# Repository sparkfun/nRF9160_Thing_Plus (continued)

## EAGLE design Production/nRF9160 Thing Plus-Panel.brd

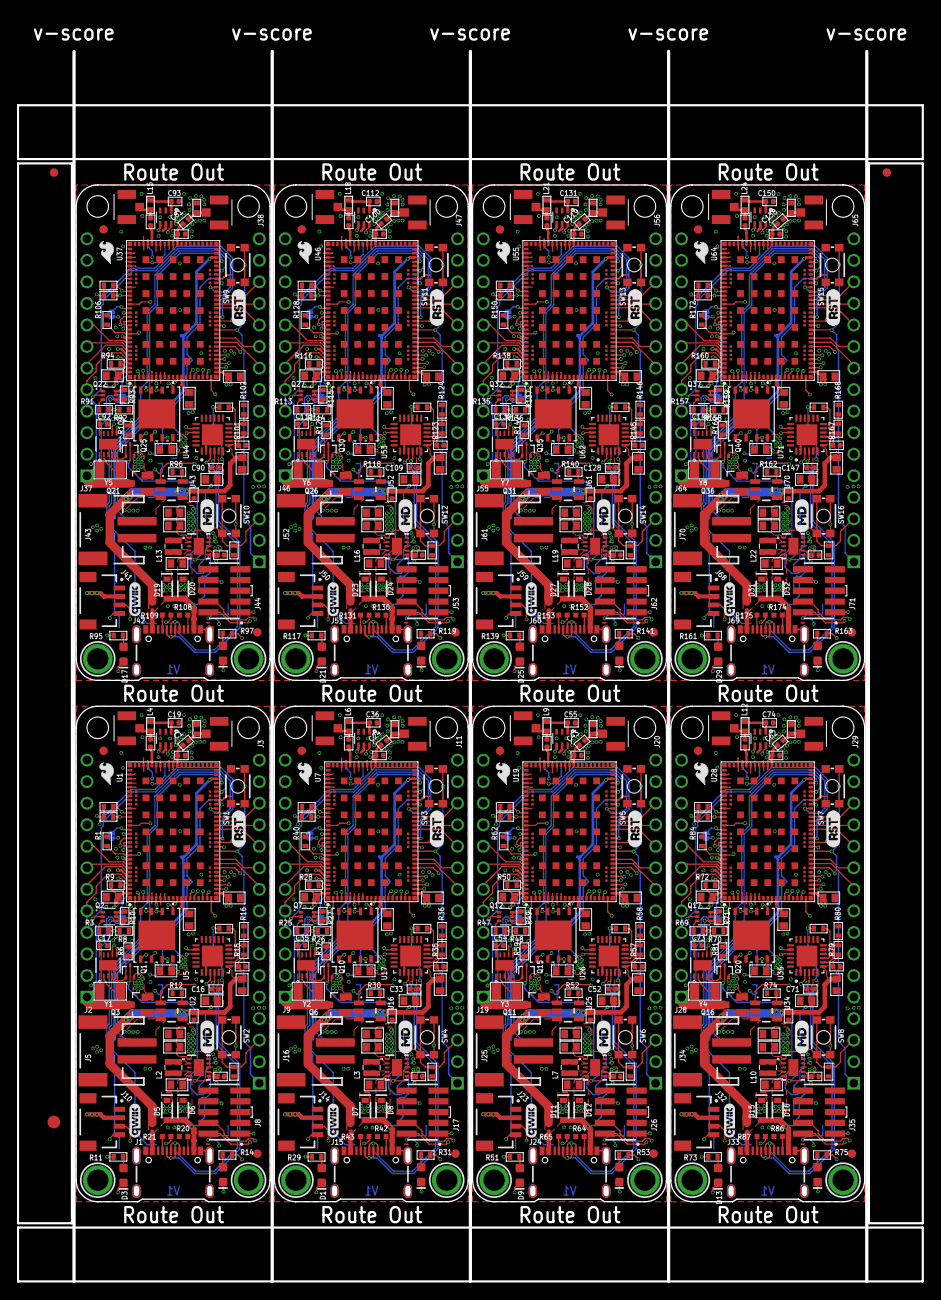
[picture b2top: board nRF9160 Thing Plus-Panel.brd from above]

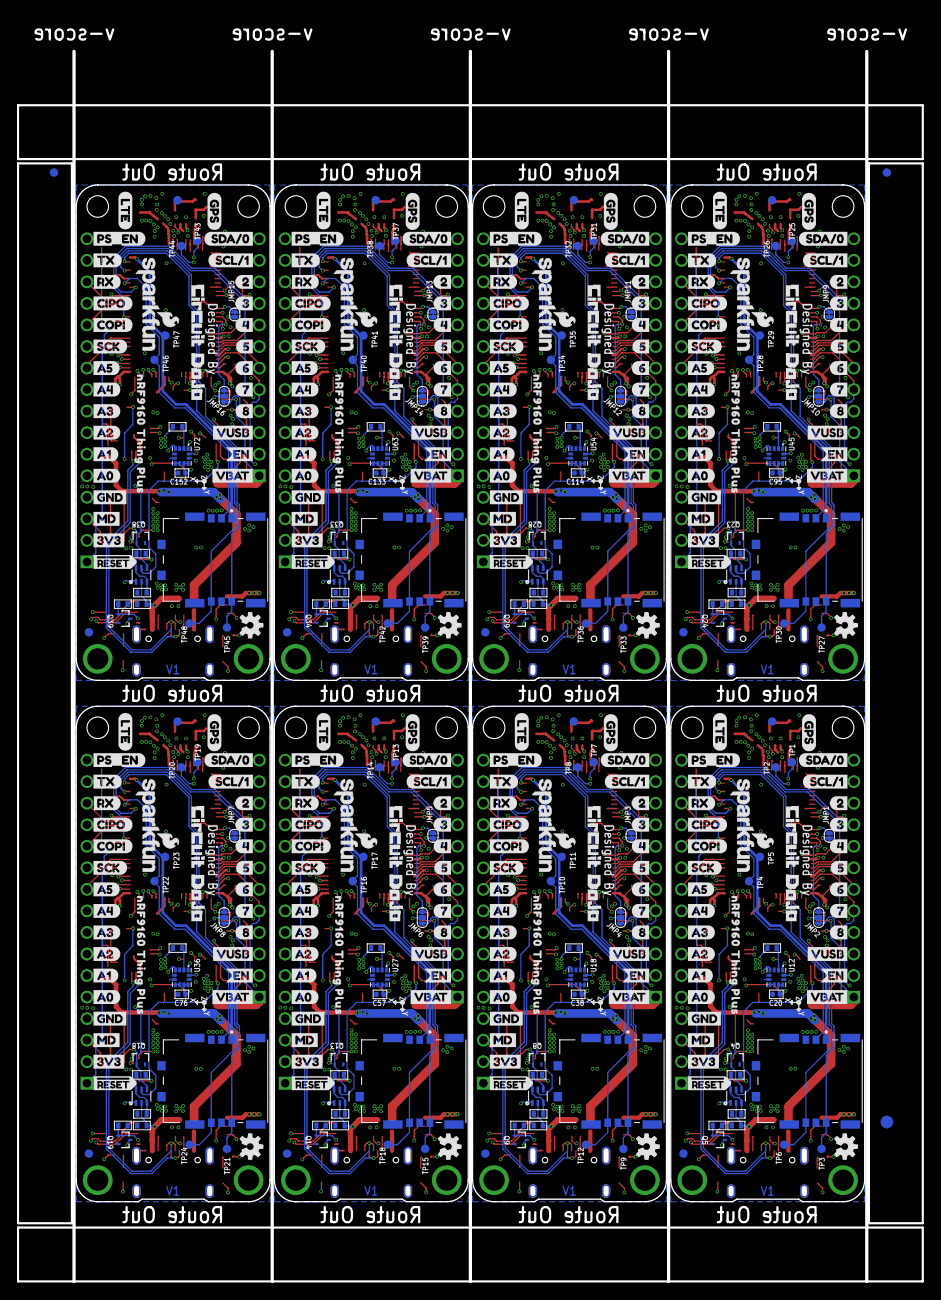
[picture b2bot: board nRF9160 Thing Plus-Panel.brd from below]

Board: 4 copper layers, 106.7 x 145.0 mm, 1030 parts (443 on the bottom side), 632 nets.

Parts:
C1, C2, C24, C37, C43, C56, C62, C75, C81, C94, C100, C113, C119, C132, C138, C151: 15p; CAPC1005X55N
C3, C8, C9, C10, C13, C15, C25, C26, C27, C28, C30, C32, C44, C45, C46, C47, C49, C51, C63, C64, C65, C66, C68, C70, C82, C83, C84, C85, C87, C89, C101, C102, C103, C104, C106, C108, C120, C121, C122, C123, C125, C127, C139, C140, C141, C142, C144, C146: 4.7u; C0603
C4, C5, C7, C18, C21, C22, C39, C40, C41, C58, C59, C60, C77, C78, C79, C96, C97, C98, C115, C116, C117, C134, C135, C136: 10u; C0603
C6, C14, C16, C17, C20, C23, C31, C33, C35, C38, C42, C50, C52, C54, C57, C61, C69, C71, C73, C76, C80, C88, C90, C92, C95, C99, C107, C109, C111, C114, C118, C126, C128, C130, C133, C137, C145, C147, C149, C152: 0.1u; CAPC1005X55N
C11, C29, C48, C67, C86, C105, C124, C143: 1u; CAPC1005X55N
C12, C19, C34, C36, C53, C55, C72, C74, C91, C93, C110, C112, C129, C131, C148, C150: 56p; CAPC1005X55N
D1, D3, D9, D13, D17, D21, D25, D29: BLUE; LED-0603
D2, D4, D10, D14, D18, D22, D26, D30: Yellow; LED-0603
D5, D6, D7, D8, D11, D12, D15, D16, D19, D20, D23, D24, D27, D28, D31, D32: 1A/23V/620mV; SOD-323
E$1, E$2, E$3, E$4: FIDUCIAL-1X2
E$5, E$6: FIDUCIAL-1.5X3
J1, J15, J24, J33, J42, J51, J60, J69: USB Female C; USB-C-16P_4LAYER-PADS
J2, J9, J19, J28, J37, J46, J55, J64: CON-HEADER-1X12-MALE-PIN
J3, J11, J20, J29, J38, J47, J56, J65: CON-HEADER-1X16-MALE-PIN
J4, J7, J12, J13, J21, J22, J30, J31, J39, J40, J48, J49, J57, J58, J66, J67: CON-1909763-1; TE_1909763-1
J5, J16, J25, J34, J43, J52, J61, J70: JST-2-SMD
J6, J18, J27, J36, J45, J54, J63, J72: CON-SIM-104224-0820; MOLEX_104224-0820
J8, J17, J26, J35, J44, J53, J62, J71: CON-FTSH-105-XX-X-DV; SAMTEC_FTSH-105-XX-X-DV
J10, J14, J23, J32, J41, J50, J59, J68: QWIIC_RIGHT_ANGLE; JST04_1MM_RA
JMP1, JMP3, JMP5, JMP7, JMP9, JMP11, JMP13, JMP15: JUMPER-NC; JUMPER-ROUND-NC
JMP2, JMP4, JMP6, JMP8, JMP10, JMP12, JMP14, JMP16: JUMPER-3/1; JUMPER-ROUND-3-NO-R
L1, L5, L8, L11, L14, L17, L20, L23: 39n; IND0402_22N_TAI
L2, L3, L7, L10, L13, L16, L19, L22: 1.5u; IND-2P0X2P0X1P2
L4, L6, L9, L12, L15, L18, L21, L24: 68n; IND0402_22N_TAI
LOGO1, LOGO2, LOGO3, LOGO4, LOGO5, LOGO6, LOGO7, LOGO8: OSHW-LOGOS; OSHW-LOGO-S
PCB1, PCB2, PCB3, PCB4, PCB5, PCB6, PCB7, PCB8: PCB-NRF91-FEATHER; PLACEHOLDER
Q1, Q10, Q15, Q20, Q25, Q30, Q35, Q40: MOSFET-P-SC89; DIO_RB558WMF-L
Q2, Q7, Q12, Q17, Q22, Q27, Q32, Q37: MOSFET-DUAL-COMP-SOT563; SOT50P160X60-6N
Q3, Q6, Q11, Q16, Q21, Q26, Q31, Q36: MOSFET-P-20V-4.7A-SOT23; SOT23
Q4, Q5, Q8, Q9, Q13, Q14, Q18, Q19, Q23, Q24, Q28, Q29, Q33, Q34, Q38, Q39: MOSFET-N-SC89; DIO_RB558WMF-L
R1, R3, R5, R6, R7, R8, R10, R13, R22, R23, R25, R26, R27, R32, R34, R37, R40, R44, R45, R47, R48, R49, R54, R56, R59, R62, R66, R67, R69, R70, R71, R76, R78, R81, R84, R88, R89, R91, R92, R93, R98, R100, R103, R106, R110, R111, R113, R114, R115, R120, R122, R125, R128, R132, R133, R135, R136, R137, R142, R144, R147, R150, R154, R155, R157, R158, R159, R164, R166, R169, R172, R176: 100k; R0402-M
R2, R9, R19, R24, R28, R41, R46, R50, R63, R68, R72, R85, R90, R94, R107, R112, R116, R129, R134, R138, R151, R156, R160, R173: 1M; R0402-M
R4, R33, R55, R77, R99, R121, R143, R165: 1k; R0402-M
R11, R14, R29, R31, R51, R53, R73, R75, R95, R97, R117, R119, R139, R141, R161, R163: 330; R0402-M
R12, R30, R52, R74, R96, R118, R140, R162: 2k; R0402-M
R15, R35, R57, R79, R101, R123, R145, R167: 22k; R0402-M
R16, R36, R58, R80, R102, R124, R146, R168: 33k; R0402-M
R17, R18, R38, R39, R60, R61, R82, R83, R104, R105, R126, R127, R148, R149, R170, R171: 10k; R0402-M
R20, R21, R42, R43, R64, R65, R86, R87, R108, R109, R130, R131, R152, R153, R174, R175: 5.1k; 0402-TIGHT
SW1, SW2, SW3, SW4, SW5, SW6, SW7, SW8, SW9, SW10, SW11, SW12, SW13, SW14, SW15, SW16: MOMENTARY-SWITCH-SPST-SMD-4.6X2.8MM; TACTILE_SWITCH_SMD_4.6X2.8MM
TP1, TP2, TP3, TP4, TP5, TP6, TP7, TP8, TP9, TP10, TP11, TP12, TP13, TP14, TP15, TP16, TP17, TP18, TP19, TP20, TP21, TP22, TP23, TP24, TP25, TP26, TP27, TP28, TP29, TP30, TP31, TP32, TP33, TP34, TP35, TP36, TP37, TP38, TP39, TP40, TP41, TP42, TP43, TP44, TP45, TP46, TP47, TP48: TP-1SIDE-1P0; TP-1P0
U1, U7, U19, U28, U37, U46, U55, U64: MOD-NRF9160-SICA-R; NORDIC_NRF9160-SICA-R
U2, U16, U25, U34, U43, U52, U61, U70: MCP73831; SOT23-5
U3, U11, U21, U30, U39, U48, U57, U66: IC-TPS63031DSKR; DSK0010A
U4, U15, U24, U33, U42, U51, U60, U69: POWER-SWITCH-MIC94092YC6; SOT363
U5, U17, U26, U35, U44, U53, U62, U71: IC-CP2102N-A02-GQFN24R; QFN50P400X400X80-25N
U6, U10, U20, U29, U38, U47, U56, U65: FLASH-WSON; WIN_ZP-8-L
U8, U13, U22, U31, U40, U49, U58, U67: IC-PCF85063ATL/1; DFN10_2P7X2P7-L
U9, U14, U23, U32, U41, U50, U59, U68: IC-BAV70S; SOT363
U12, U18, U27, U36, U45, U54, U63, U72: IC-LIS2DH12TR; PQFN50P200X200100-12N
U$1, U$66, U$127, U$171, U$215, U$259, U$303, U$347: SFE_LOGO_NAME_FLAME_.1
U$2, U$28, U$81, U$136, U$180, U$224, U$268, U$312: LOGO-CIRCUITDOJO
U$3, U$4, U$24, U$25, U$29, U$30, U$35, U$77, U$78, U$82, U$94, U$132, U$133, U$137, U$138, U$176, U$177, U$181, U$182, U$220, U$221, U$225, U$226, U$264, U$265, U$269, U$270, U$308, U$309, U$313, U$314, U$352: FIDUCIAL-1MM
U$5, U$33, U$95, U$139, U$183, U$227, U$271, U$315: A3L-LOC
U$6, U$34, U$96, U$140, U$184, U$228, U$272, U$316: QWIIC_4MM
U$7, U$61, U$122, U$166, U$210, U$254, U$298, U$342: RST0
U$8, U$67, U$128, U$172, U$216, U$260, U$304, U$348: PS_EN0
U$9, U$14, U$55, U$62, U$116, U$123, U$160, U$167, U$204, U$211, U$248, U$255, U$292, U$299, U$336, U$343: MD0
U$10, U$53, U$114, U$158, U$202, U$246, U$290, U$334: 20
U$11, U$54, U$115, U$159, U$203, U$247, U$291, U$335: 30
U$12, U$70, U$130, U$174, U$218, U$262, U$306, U$350: SCL#11
U$13, U$76, U$131, U$175, U$219, U$263, U$307, U$351: SDA#00
U$15, U$63, U$124, U$168, U$212, U$256, U$300, U$344: SFE_LOGO_FLAME_.1
U$16, U$56, U$117, U$161, U$205, U$249, U$293, U$337: TX0
U$17, U$57, U$118, U$162, U$206, U$250, U$294, U$338: RX0
U$18, U$58, U$119, U$163, U$207, U$251, U$295, U$339: SCK0
U$19, U$59, U$120, U$164, U$208, U$252, U$296, U$340: CIPO0
U$20, U$60, U$121, U$165, U$209, U$253, U$297, U$341: COPI0
U$21, U$64, U$125, U$169, U$213, U$257, U$301, U$345: GPS0
U$22, U$65, U$126, U$170, U$214, U$258, U$302, U$346: LTE0
U$23, U$68, U$129, U$173, U$217, U$261, U$305, U$349: NRF9160_THING_PLUS0
U$26, U$27, U$31, U$32, U$79, U$80, U$134, U$135, U$178, U$179, U$222, U$223, U$266, U$267, U$310, U$311: MOUNTING-HOLE-2.5MM-PLATED
U$36, U$69, U$97, U$141, U$185, U$229, U$273, U$317: GND12
U$37, U$71, U$98, U$142, U$186, U$230, U$274, U$318: 3V314
U$38, U$72, U$99, U$143, U$187, U$231, U$275, U$319: #RESET15
U$39, U$73, U$100, U$144, U$188, U$232, U$276, U$320: VUSB25
U$40, U$74, U$101, U$145, U$189, U$233, U$277, U$321: EN26
U$41, U$75, U$102, U$146, U$190, U$234, U$278, U$322: VBAT27
U$42, U$83, U$103, U$147, U$191, U$235, U$279, U$323: A56
U$43, U$84, U$104, U$148, U$192, U$236, U$280, U$324: A47
U$44, U$85, U$105, U$149, U$193, U$237, U$281, U$325: A38
U$45, U$86, U$106, U$150, U$194, U$238, U$282, U$326: A29
U$46, U$87, U$107, U$151, U$195, U$239, U$283, U$327: A110
U$47, U$88, U$108, U$152, U$196, U$240, U$284, U$328: A011
U$48, U$89, U$109, U$153, U$197, U$241, U$285, U$329: 412
U$49, U$90, U$110, U$154, U$198, U$242, U$286, U$330: 513
U$50, U$91, U$111, U$155, U$199, U$243, U$287, U$331: 614
U$51, U$92, U$112, U$156, U$200, U$244, U$288, U$332: 715
U$52, U$93, U$113, U$157, U$201, U$245, U$289, U$333: 816
Y1, Y2, Y3, Y4, Y5, Y6, Y7, Y8: XTAL-ABS07AIG-32.768KHZ-7-T; XTAL320X150X90

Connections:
!EN: J2.2, Q5.1, R19.2
!EN1: J9.2, Q9.1, R41.2
!EN2: J19.2, Q14.1, R63.2
!EN3: J28.2, Q19.1, R85.2
!EN4: J37.2, Q24.1, R107.2
!EN5: J46.2, Q29.1, R129.2
!EN6: J55.2, Q34.1, R151.2
!EN7: J64.2, Q39.1, R173.2
!RESET: J3.1, SW1.1, SW1.2, U1.32
!RESET1: J11.1, SW3.1, SW3.2, U7.32
!RESET2: J20.1, SW5.1, SW5.2, U19.32
!RESET3: J29.1, SW7.1, SW7.2, U28.32
!RESET4: J38.1, SW9.1, SW9.2, U37.32
!RESET5: J47.1, SW11.1, SW11.2, U46.32
!RESET6: J56.1, SW13.1, SW13.2, U55.32
!RESET7: J65.1, SW15.1, SW15.2, U64.32
+3V1: C18.1, C21.1, C25.1, C26.1, C28.1, C38.1, J11.2, J14.2, J17.1, R28.2, R29.2, R31.2, R38.2, R39.2, R44.2, U7.12, U7.22, U7.102, U10.8, U11.1, U11.10, U15.4, U18.9, U18.10
+3V2: C39.1, C40.1, C44.1, C45.1, C47.1, C57.1, J20.2, J23.2, J26.1, R50.2, R51.2, R53.2, R60.2, R61.2, R66.2, U19.12, U19.22, U19.102, U20.8, U21.1, U21.10, U24.4, U27.9, U27.10
+3V3: C3.1, C4.1, C5.1, C8.1, C10.1, C20.1, J3.2, J8.1, J10.2, R9.2, R11.2, R14.2, R17.2, R18.2, R23.2, U1.12, U1.22, U1.102, U3.1, U3.10, U4.4, U6.8, U12.9, U12.10
+3V4: C58.1, C59.1, C63.1, C64.1, C66.1, C76.1, J29.2, J32.2, J35.1, R72.2, R73.2, R75.2, R82.2, R83.2, R88.2, U28.12, U28.22, U28.102, U29.8, U30.1, U30.10, U33.4, U36.9, U36.10
+3V5: C77.1, C78.1, C82.1, C83.1, C85.1, C95.1, J38.2, J41.2, J44.1, R94.2, R95.2, R97.2, R104.2, R105.2, R110.2, U37.12, U37.22, U37.102, U38.8, U39.1, U39.10, U42.4, U45.9, U45.10
+3V6: C96.1, C97.1, C101.1, C102.1, C104.1, C114.1, J47.2, J50.2, J53.1, R116.2, R117.2, R119.2, R126.2, R127.2, R132.2, U46.12, U46.22, U46.102, U47.8, U48.1, U48.10, U51.4, U54.9, U54.10
+3V7: C115.1, C116.1, C120.1, C121.1, C123.1, C133.1, J56.2, J59.2, J62.1, R138.2, R139.2, R141.2, R148.2, R149.2, R154.2, U55.12, U55.22, U55.102, U56.8, U57.1, U57.10, U60.4, U63.9, U63.10
+3V8: C134.1, C135.1, C139.1, C140.1, C142.1, C152.1, J65.2, J68.2, J71.1, R160.2, R161.2, R163.2, R170.2, R171.2, R176.2, U64.12, U64.22, U64.102, U65.8, U66.1, U66.10, U69.4, U72.9, U72.10
ANT: C1.2, C2.1, U1.61
ANT1: C24.2, C37.1, U7.61
ANT2: C43.2, C56.1, U19.61
ANT3: C62.2, C75.1, U28.61
ANT4: C81.2, C94.1, U37.61
ANT5: C100.2, C113.1, U46.61
ANT6: C119.2, C132.1, U55.61
ANT7: C138.2, C151.1, U64.61
ANT_FILT: C1.1, J4.1, L1.2
ANT_FILT1: C24.1, J12.1, L5.2
ANT_FILT2: C43.1, J21.1, L8.2
ANT_FILT3: C62.1, J30.1, L11.2
ANT_FILT4: C81.1, J39.1, L14.2
ANT_FILT5: C100.1, J48.1, L17.2
ANT_FILT6: C119.1, J57.1, L20.2
ANT_FILT7: C138.1, J66.1, L23.2
CHRG: D4.C, U2.1
CHRG1: D2.C, U16.1
CHRG2: D10.C, U25.1
CHRG3: D14.C, U34.1
CHRG4: D18.C, U43.1
CHRG5: D22.C, U52.1
CHRG6: D26.C, U61.1
CHRG7: D30.C, U70.1
COEX0/LNA_EN: R1.2, U1.93, U4.6
COEX0/LNA_EN1: R40.2, U7.93, U15.6
COEX0/LNA_EN2: R62.2, U19.93, U24.6
COEX0/LNA_EN3: R84.2, U28.93, U33.6
COEX0/LNA_EN4: R106.2, U37.93, U42.6
COEX0/LNA_EN5: R128.2, U46.93, U51.6
COEX0/LNA_EN6: R150.2, U55.93, U60.6
COEX0/LNA_EN7: R172.2, U64.93, U69.6
CP212_VBUS: R15.1, R16.2, U5.8
CP212_VBUS1: R35.1, R36.2, U17.8
CP212_VBUS2: R57.1, R58.2, U26.8
CP212_VBUS3: R79.1, R80.2, U35.8
CP212_VBUS4: R101.1, R102.2, U44.8
CP212_VBUS5: R123.1, R124.2, U53.8
CP212_VBUS6: R145.1, R146.2, U62.8
CP212_VBUS7: R167.1, R168.2, U71.8
CP2102N-!RST: R4.1, U5.9
CP2102N-!RST1: R33.1, U17.9
CP2102N-!RST2: R55.1, U26.9
CP2102N-!RST3: R77.1, U35.9
CP2102N-!RST4: R99.1, U44.9
CP2102N-!RST5: R121.1, U53.9
CP2102N-!RST6: R143.1, U62.9
CP2102N-!RST7: R165.1, U71.9
CP2102N-VDD: C15.1, C16.1, R4.2, U5.5, U5.6
CP2102N-VDD1: C32.1, C33.1, R33.2, U17.5, U17.6
CP2102N-VDD2: C51.1, C52.1, R55.2, U26.5, U26.6
CP2102N-VDD3: C70.1, C71.1, R77.2, U35.5, U35.6
CP2102N-VDD4: C89.1, C90.1, R99.2, U44.5, U44.6
CP2102N-VDD5: C108.1, C109.1, R121.2, U53.5, U53.6
CP2102N-VDD6: C127.1, C128.1, R143.2, U62.5, U62.6
CP2102N-VDD7: C146.1, C147.1, R165.2, U71.5, U71.6
DIFF_N: J1.A7, J1.B7, U5.4
DIFF_N1: J15.A7, J15.B7, U17.4
DIFF_N2: J24.A7, J24.B7, U26.4
DIFF_N3: J33.A7, J33.B7, U35.4
DIFF_N4: J42.A7, J42.B7, U44.4
DIFF_N5: J51.A7, J51.B7, U53.4
DIFF_N6: J60.A7, J60.B7, U62.4
DIFF_N7: J69.A7, J69.B7, U71.4
DIFF_P: J1.A6, J1.B6, U5.3
DIFF_P1: J15.A6, J15.B6, U17.3
DIFF_P2: J24.A6, J24.B6, U26.3
DIFF_P3: J33.A6, J33.B6, U35.3
DIFF_P4: J42.A6, J42.B6, U44.3
DIFF_P5: J51.A6, J51.B6, U53.3
DIFF_P6: J60.A6, J60.B6, U62.3
DIFF_P7: J69.A6, J69.B6, U71.3
FLASH_CS: U1.4, U6.1
FLASH_CS1: U7.4, U10.1
FLASH_CS2: U19.4, U20.1
FLASH_CS3: U28.4, U29.1
FLASH_CS4: U37.4, U38.1
FLASH_CS5: U46.4, U47.1
FLASH_CS6: U55.4, U56.1
FLASH_CS7: U64.4, U65.1
FLASH_HOLD: U1.18, U6.7
FLASH_HOLD1: U7.18, U10.7
FLASH_HOLD2: U19.18, U20.7
FLASH_HOLD3: U28.18, U29.7
FLASH_HOLD4: U37.18, U38.7
FLASH_HOLD5: U46.18, U47.7
FLASH_HOLD6: U55.18, U56.7
FLASH_HOLD7: U64.18, U65.7
FLASH_SCK: U1.19, U6.6
FLASH_SCK1: U7.19, U10.6
FLASH_SCK2: U19.19, U20.6
FLASH_SCK3: U28.19, U29.6
FLASH_SCK4: U37.19, U38.6
FLASH_SCK5: U46.19, U47.6
FLASH_SCK6: U55.19, U56.6
FLASH_SCK7: U64.19, U65.6
FLASH_SI: U1.16, U6.5
FLASH_SI1: U7.16, U10.5
FLASH_SI2: U19.16, U20.5
FLASH_SI3: U28.16, U29.5
FLASH_SI4: U37.16, U38.5
FLASH_SI5: U46.16, U47.5
FLASH_SI6: U55.16, U56.5
FLASH_SI7: U64.16, U65.5
FLASH_SO: U1.86, U6.2
FLASH_SO1: U7.86, U10.2
FLASH_SO2: U19.86, U20.2
FLASH_SO3: U28.86, U29.2
FLASH_SO4: U37.86, U38.2
FLASH_SO5: U46.86, U47.2
FLASH_SO6: U55.86, U56.2
FLASH_SO7: U64.86, U65.2
FLASH_WP: U1.15, U6.3
FLASH_WP1: U7.15, U10.3
FLASH_WP2: U19.15, U20.3
FLASH_WP3: U28.15, U29.3
FLASH_WP4: U37.15, U38.3
FLASH_WP5: U46.15, U47.3
FLASH_WP6: U55.15, U56.3
FLASH_WP7: U64.15, U65.3
GND: C2.2, C3.2, C4.2, C5.2, C6.2, C7.2, C8.2, C9.2, C10.2, C11.2, C13.2, C14.2, C15.2, C16.2, C17.2, C19.2, C20.2, J1.GND, J1.GND2, J1.SHLD1, J1.SHLD2, J1.SHLD3, J1.SHLD4, J3.4, J4.2, J4.3, J5.1, J6.G1, J6.G2, J6.G3, J6.G4, J6.S4, J7.2, J7.3, J8.3, J8.5, J8.9, J10.1, L1.1, Q2.1, Q4.2, Q5.2, R1.1, R2.1, R7.1, R8.1, R12.1, R13.1, R16.1, R19.1, R20.1, R21.1, SW1.3, SW1.4, U1.1, U1.5, U1.6, U1.7, U1.8, U1.9, U1.11, U1.14, U1.17, U1.21, U1.27, U1.31, U1.36, U1.41, U1.44, U1.47, U1.50, U1.52, U1.56, U1.60, U1.62, U1.63, U1.65, U1.66, U1.68, U1.69, U1.72, U1.74, U1.75, U1.76, U1.77, U1.78, U1.79, U1.80, U1.81, U1.82, U1.85, U1.90, U1.94, U1.98, U1.103_1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
GND1: C18.2, C21.2, C22.2, C23.2, C25.2, C26.2, C27.2, C28.2, C29.2, C30.2, C31.2, C32.2, C33.2, C35.2, C36.2, C37.2, C38.2, J11.4, J12.2, J12.3, J13.2, J13.3, J14.1, J15.GND, J15.GND2, J15.SHLD1, J15.SHLD2, J15.SHLD3, J15.SHLD4, J16.1, J17.3, J17.5, J17.9, J18.G1, J18.G2, J18.G3, J18.G4, J18.S4, L5.1, Q7.1, Q8.2, Q9.2, R22.1, R24.1, R26.1, R30.1, R32.1, R36.1, R40.1, R41.1, R42.1, R43.1, SW3.3, SW3.4, U7.1, U7.5, U7.6, U7.7, U7.8, U7.9, U7.11, U7.14, U7.17, U7.21, U7.27, U7.31, U7.36, U7.41, U7.44, U7.47, U7.50, U7.52, U7.56, U7.60, U7.62, U7.63, U7.65, U7.66, U7.68, U7.69, U7.72, U7.74, U7.75, U7.76, U7.77, U7.78, U7.79, U7.80, U7.81, U7.82, U7.85, U7.90, U7.94, U7.98, U7.103_1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
GND2: C39.2, C40.2, C41.2, C42.2, C44.2, C45.2, C46.2, C47.2, C48.2, C49.2, C50.2, C51.2, C52.2, C54.2, C55.2, C56.2, C57.2, J20.4, J21.2, J21.3, J22.2, J22.3, J23.1, J24.GND, J24.GND2, J24.SHLD1, J24.SHLD2, J24.SHLD3, J24.SHLD4, J25.1, J26.3, J26.5, J26.9, J27.G1, J27.G2, J27.G3, J27.G4, J27.S4, L8.1, Q12.1, Q13.2, Q14.2, R45.1, R46.1, R48.1, R52.1, R54.1, R58.1, R62.1, R63.1, R64.1, R65.1, SW5.3, SW5.4, U19.1, U19.5, U19.6, U19.7, U19.8, U19.9, U19.11, U19.14, U19.17, U19.21, U19.27, U19.31, U19.36, U19.41, U19.44, U19.47, U19.50, U19.52, U19.56, U19.60, U19.62, U19.63, U19.65, U19.66, U19.68, U19.69, U19.72, U19.74, U19.75, U19.76, U19.77, U19.78, U19.79, U19.80, U19.81, U19.82, U19.85, U19.90, U19.94, U19.98, U19.103_1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
GND3: C58.2, C59.2, C60.2, C61.2, C63.2, C64.2, C65.2, C66.2, C67.2, C68.2, C69.2, C70.2, C71.2, C73.2, C74.2, C75.2, C76.2, J29.4, J30.2, J30.3, J31.2, J31.3, J32.1, J33.GND, J33.GND2, J33.SHLD1, J33.SHLD2, J33.SHLD3, J33.SHLD4, J34.1, J35.3, J35.5, J35.9, J36.G1, J36.G2, J36.G3, J36.G4, J36.S4, L11.1, Q17.1, Q18.2, Q19.2, R67.1, R68.1, R70.1, R74.1, R76.1, R80.1, R84.1, R85.1, R86.1, R87.1, SW7.3, SW7.4, U28.1, U28.5, U28.6, U28.7, U28.8, U28.9, U28.11, U28.14, U28.17, U28.21, U28.27, U28.31, U28.36, U28.41, U28.44, U28.47, U28.50, U28.52, U28.56, U28.60, U28.62, U28.63, U28.65, U28.66, U28.68, U28.69, U28.72, U28.74, U28.75, U28.76, U28.77, U28.78, U28.79, U28.80, U28.81, U28.82, U28.85, U28.90, U28.94, U28.98, U28.103_1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
GND4: C77.2, C78.2, C79.2, C80.2, C82.2, C83.2, C84.2, C85.2, C86.2, C87.2, C88.2, C89.2, C90.2, C92.2, C93.2, C94.2, C95.2, J38.4, J39.2, J39.3, J40.2, J40.3, J41.1, J42.GND, J42.GND2, J42.SHLD1, J42.SHLD2, J42.SHLD3, J42.SHLD4, J43.1, J44.3, J44.5, J44.9, J45.G1, J45.G2, J45.G3, J45.G4, J45.S4, L14.1, Q22.1, Q23.2, Q24.2, R89.1, R90.1, R92.1, R96.1, R98.1, R102.1, R106.1, R107.1, R108.1, R109.1, SW9.3, SW9.4, U37.1, U37.5, U37.6, U37.7, U37.8, U37.9, U37.11, U37.14, U37.17, U37.21, U37.27, U37.31, U37.36, U37.41, U37.44, U37.47, U37.50, U37.52, U37.56, U37.60, U37.62, U37.63, U37.65, U37.66, U37.68, U37.69, U37.72, U37.74, U37.75, U37.76, U37.77, U37.78, U37.79, U37.80, U37.81, U37.82, U37.85, U37.90, U37.94, U37.98, U37.103_1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
GND5: C96.2, C97.2, C98.2, C99.2, C101.2, C102.2, C103.2, C104.2, C105.2, C106.2, C107.2, C108.2, C109.2, C111.2, C112.2, C113.2, C114.2, J47.4, J48.2, J48.3, J49.2, J49.3, J50.1, J51.GND, J51.GND2, J51.SHLD1, J51.SHLD2, J51.SHLD3, J51.SHLD4, J52.1, J53.3, J53.5, J53.9, J54.G1, J54.G2, J54.G3, J54.G4, J54.S4, L17.1, Q27.1, Q28.2, Q29.2, R111.1, R112.1, R114.1, R118.1, R120.1, R124.1, R128.1, R129.1, R130.1, R131.1, SW11.3, SW11.4, U46.1, U46.5, U46.6, U46.7, U46.8, U46.9, U46.11, U46.14, U46.17, U46.21, U46.27, U46.31, U46.36, U46.41, U46.44, U46.47, U46.50, U46.52, U46.56, U46.60, U46.62, U46.63, U46.65, U46.66, U46.68, U46.69, U46.72, U46.74, U46.75, U46.76, U46.77, U46.78, U46.79, U46.80, U46.81, U46.82, U46.85, U46.90, U46.94, U46.98, U46.103_1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
GND6: C115.2, C116.2, C117.2, C118.2, C120.2, C121.2, C122.2, C123.2, C124.2, C125.2, C126.2, C127.2, C128.2, C130.2, C131.2, C132.2, C133.2, J56.4, J57.2, J57.3, J58.2, J58.3, J59.1, J60.GND, J60.GND2, J60.SHLD1, J60.SHLD2, J60.SHLD3, J60.SHLD4, J61.1, J62.3, J62.5, J62.9, J63.G1, J63.G2, J63.G3, J63.G4, J63.S4, L20.1, Q32.1, Q33.2, Q34.2, R133.1, R134.1, R136.1, R140.1, R142.1, R146.1, R150.1, R151.1, R152.1, R153.1, SW13.3, SW13.4, U55.1, U55.5, U55.6, U55.7, U55.8, U55.9, U55.11, U55.14, U55.17, U55.21, U55.27, U55.31, U55.36, U55.41, U55.44, U55.47, U55.50, U55.52, U55.56, U55.60, U55.62, U55.63, U55.65, U55.66, U55.68, U55.69, U55.72, U55.74, U55.75, U55.76, U55.77, U55.78, U55.79, U55.80, U55.81, U55.82, U55.85, U55.90, U55.94, U55.98, U55.103_1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
GND7: C134.2, C135.2, C136.2, C137.2, C139.2, C140.2, C141.2, C142.2, C143.2, C144.2, C145.2, C146.2, C147.2, C149.2, C150.2, C151.2, C152.2, J65.4, J66.2, J66.3, J67.2, J67.3, J68.1, J69.GND, J69.GND2, J69.SHLD1, J69.SHLD2, J69.SHLD3, J69.SHLD4, J70.1, J71.3, J71.5, J71.9, J72.G1, J72.G2, J72.G3, J72.G4, J72.S4, L23.1, Q37.1, Q38.2, Q39.2, R155.1, R156.1, R158.1, R162.1, R164.1, R168.1, R172.1, R173.1, R174.1, R175.1, SW15.3, SW15.4, U64.1, U64.5, U64.6, U64.7, U64.8, U64.9, U64.11, U64.14, U64.17, U64.21, U64.27, U64.31, U64.36, U64.41, U64.44, U64.47, U64.50, U64.52, U64.56, U64.60, U64.62, U64.63, U64.65, U64.66, U64.68, U64.69, U64.72, U64.74, U64.75, U64.76, U64.77, U64.78, U64.79, U64.80, U64.81, U64.82, U64.85, U64.90, U64.94, U64.98, U64.103_1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
GPS: C12.1, U1.67
GPS1: C34.1, U7.67
GPS2: C53.1, U19.67
GPS3: C72.1, U28.67
GPS4: C91.1, U37.67
GPS5: C110.1, U46.67
GPS6: C129.1, U55.67
GPS7: C148.1, U64.67
GPS_ANT: C12.2, J7.1, L4.2
GPS_ANT1: C34.2, J13.1, L6.2
GPS_ANT2: C53.2, J22.1, L9.2
GPS_ANT3: C72.2, J31.1, L12.2
GPS_ANT4: C91.2, J40.1, L15.2
GPS_ANT5: C110.2, J49.1, L18.2
GPS_ANT6: C129.2, J58.1, L21.2
GPS_ANT7: C148.2, J67.1, L24.2
LNA_SW_OUT: C19.1, L4.1, U4.1
LNA_SW_OUT1: C36.1, L6.1, U15.1
LNA_SW_OUT2: C55.1, L9.1, U24.1
LNA_SW_OUT3: C74.1, L12.1, U33.1
LNA_SW_OUT4: C93.1, L15.1, U42.1
LNA_SW_OUT5: C112.1, L18.1, U51.1
LNA_SW_OUT6: C131.1, L21.1, U60.1
LNA_SW_OUT7: C150.1, L24.1, U69.1
MODE/WAKE: J3.3, Q4.1, R13.2, SW2.3, SW2.4, U9.4
MODE/WAKE1: J11.3, Q8.1, R32.2, SW4.3, SW4.4, U14.4
MODE/WAKE2: J20.3, Q13.1, R54.2, SW6.3, SW6.4, U23.4
MODE/WAKE3: J29.3, Q18.1, R76.2, SW8.3, SW8.4, U32.4
MODE/WAKE4: J38.3, Q23.1, R98.2, SW10.3, SW10.4, U41.4
MODE/WAKE5: J47.3, Q28.1, R120.2, SW12.3, SW12.4, U50.4
MODE/WAKE6: J56.3, Q33.1, R142.2, SW14.3, SW14.4, U59.4
MODE/WAKE7: J65.3, Q38.1, R164.2, SW16.3, SW16.4, U68.4
unnamed: L2.P$1, U3.4
unnamed: L2.P$2, U3.2
unnamed: J1.A5, R21.2
unnamed: R9.1, U1.101
unnamed: C9.1, U1.13
unnamed: Q2.3, R3.2
unnamed: Q2.5, Q2.6, R10.1
unnamed: D3.A, R11.1
unnamed: J1.B5, R20.2
unnamed: U8.1, Y1.2
unnamed: R23.1, U12.2
unnamed: JMP1.P$1, U12.12
unnamed: D4.A, R14.1
unnamed: L3.P$1, U11.4
unnamed: L3.P$2, U11.2
unnamed: Q7.3, R25.2
unnamed: Q7.5, Q7.6, R27.1
unnamed: U8.2, Y1.1
unnamed: C27.1, U7.13
unnamed: R28.1, U7.101
unnamed: D1.A, R29.1
unnamed: D2.A, R31.1
unnamed: U13.1, Y2.2
unnamed: U13.2, Y2.1
unnamed: J15.A5, R43.2
unnamed: J15.B5, R42.2
unnamed: R44.1, U18.2
unnamed: JMP3.P$1, U18.12
unnamed: L7.P$1, U21.4
unnamed: L7.P$2, U21.2
unnamed: Q12.3, R47.2
unnamed: Q12.5, Q12.6, R49.1
unnamed: C46.1, U19.13
unnamed: R50.1, U19.101
unnamed: D9.A, R51.1
unnamed: D10.A, R53.1
unnamed: U22.1, Y3.2
unnamed: U22.2, Y3.1
unnamed: J24.A5, R65.2
unnamed: J24.B5, R64.2
unnamed: R66.1, U27.2
unnamed: JMP5.P$1, U27.12
unnamed: L10.P$1, U30.4
unnamed: L10.P$2, U30.2
unnamed: Q17.3, R69.2
unnamed: Q17.5, Q17.6, R71.1
unnamed: C65.1, U28.13
unnamed: R72.1, U28.101
unnamed: D13.A, R73.1
unnamed: D14.A, R75.1
unnamed: U31.1, Y4.2
unnamed: U31.2, Y4.1
unnamed: J33.A5, R87.2
unnamed: J33.B5, R86.2
unnamed: R88.1, U36.2
unnamed: JMP7.P$1, U36.12
unnamed: L13.P$1, U39.4
unnamed: L13.P$2, U39.2
unnamed: Q22.3, R91.2
unnamed: Q22.5, Q22.6, R93.1
unnamed: C84.1, U37.13
unnamed: R94.1, U37.101
unnamed: D17.A, R95.1
unnamed: D18.A, R97.1
unnamed: U40.1, Y5.2
unnamed: U40.2, Y5.1
unnamed: J42.A5, R109.2
unnamed: J42.B5, R108.2
unnamed: R110.1, U45.2
unnamed: JMP9.P$1, U45.12
unnamed: L16.P$1, U48.4
unnamed: L16.P$2, U48.2
unnamed: Q27.3, R113.2
unnamed: Q27.5, Q27.6, R115.1
unnamed: C103.1, U46.13
unnamed: R116.1, U46.101
unnamed: D21.A, R117.1
unnamed: D22.A, R119.1
unnamed: U49.1, Y6.2
unnamed: U49.2, Y6.1
unnamed: J51.A5, R131.2
unnamed: J51.B5, R130.2
unnamed: R132.1, U54.2
unnamed: JMP11.P$1, U54.12
unnamed: L19.P$1, U57.4
unnamed: L19.P$2, U57.2
unnamed: Q32.3, R135.2
unnamed: Q32.5, Q32.6, R137.1
unnamed: C122.1, U55.13
unnamed: R138.1, U55.101
unnamed: D25.A, R139.1
unnamed: D26.A, R141.1
unnamed: U58.1, Y7.2
unnamed: U58.2, Y7.1
unnamed: J60.A5, R153.2
unnamed: J60.B5, R152.2
unnamed: R154.1, U63.2
unnamed: JMP13.P$1, U63.12
unnamed: L22.P$1, U66.4
unnamed: L22.P$2, U66.2
unnamed: Q37.3, R157.2
unnamed: Q37.5, Q37.6, R159.1
unnamed: C141.1, U64.13
unnamed: R160.1, U64.101
unnamed: D29.A, R161.1
unnamed: D30.A, R163.1
unnamed: U67.1, Y8.2
unnamed: U67.2, Y8.1
unnamed: J69.A5, R175.2
unnamed: J69.B5, R174.2
unnamed: R176.1, U72.2
unnamed: JMP15.P$1, U72.12
NRF_PS_EN_JMP: JMP2.P$2, U9.1
NRF_PS_EN_JMP1: JMP4.P$2, U14.1
NRF_PS_EN_JMP2: JMP6.P$2, U23.1
NRF_PS_EN_JMP3: JMP8.P$2, U32.1
NRF_PS_EN_JMP4: JMP10.P$2, U41.1
NRF_PS_EN_JMP5: JMP12.P$2, U50.1
NRF_PS_EN_JMP6: JMP14.P$2, U59.1
NRF_PS_EN_JMP7: JMP16.P$2, U68.1
P0.00/D1: J9.8, U7.95
P0.00/D2: J19.8, U19.95
P0.00/D3: J28.8, U28.95
P0.00/D4: J2.8, U1.95
P0.00/D5: J37.8, U37.95
P0.00/D6: J46.8, U46.95
P0.00/D7: J55.8, U55.95
P0.00/D8: J64.8, U64.95
P0.01/D1: J9.7, U7.96
P0.01/D2: J19.7, U19.96
P0.01/D3: J28.7, U28.96
P0.01/D4: J37.7, U37.96
P0.01/D5: J2.7, U1.96
P0.01/D6: J46.7, U46.96
P0.01/D7: J55.7, U55.96
P0.01/D8: J64.7, U64.96
P0.02/D1: J9.6, U7.97
P0.02/D2: J19.6, U19.97
P0.02/D3: J28.6, U28.97
P0.02/D4: J37.6, U37.97
P0.02/D5: J46.6, U46.97
P0.02/D6: J2.6, U1.97
P0.02/D7: J55.6, U55.97
P0.02/D8: J64.6, U64.97
P0.03/D1: D1.C, J9.5, U7.99
P0.03/D2: D9.C, J19.5, U19.99
P0.03/D3: D13.C, J28.5, U28.99
P0.03/D4: D17.C, J37.5, U37.99
P0.03/D5: D21.C, J46.5, U46.99
P0.03/D6: D25.C, J55.5, U55.99
P0.03/D7: D3.C, J2.5, U1.99
P0.03/D8: D29.C, J64.5, U64.99
P0.04/D1: J9.4, U7.100
P0.04/D2: J19.4, U19.100
P0.04/D3: J28.4, U28.100
P0.04/D4: J37.4, U37.100
P0.04/D5: J46.4, U46.100
P0.04/D6: J55.4, U55.100
P0.04/D7: J64.4, U64.100
P0.04/D8: J2.4, U1.100
P0.05/USB_UART_RX: U1.2, U5.21
P0.05/USB_UART_RX1: U7.2, U17.21
P0.05/USB_UART_RX2: U19.2, U26.21
P0.05/USB_UART_RX3: U28.2, U35.21
P0.05/USB_UART_RX4: U37.2, U44.21
P0.05/USB_UART_RX5: U46.2, U53.21
P0.05/USB_UART_RX6: U55.2, U62.21
P0.05/USB_UART_RX7: U64.2, U71.21
P0.06/USB_UART_TX: U1.3, U5.20
P0.06/USB_UART_TX1: U7.3, U17.20
P0.06/USB_UART_TX2: U19.3, U26.20
P0.06/USB_UART_TX3: U28.3, U35.20
P0.06/USB_UART_TX4: U37.3, U44.20
P0.06/USB_UART_TX5: U46.3, U53.20
P0.06/USB_UART_TX6: U55.3, U62.20
P0.06/USB_UART_TX7: U64.3, U71.20
P0.12/MD: Q4.3, U1.20
P0.12/MD1: Q8.3, U7.20
P0.12/MD2: Q13.3, U19.20
P0.12/MD3: Q18.3, U28.20
P0.12/MD4: Q23.3, U37.20
P0.12/MD5: Q28.3, U46.20
P0.12/MD6: Q33.3, U55.20
P0.12/MD7: Q38.3, U64.20
P0.13/A0: J3.5, U1.23
P0.13/A1: J11.5, U7.23
P0.13/A2: J20.5, U19.23
P0.13/A3: J29.5, U28.23
P0.13/A4: J38.5, U37.23
P0.13/A5: J47.5, U46.23
P0.13/A6: J56.5, U55.23
P0.13/A7: J65.5, U64.23
P0.14/A1: J3.6, U1.24
P0.14/A2: J11.6, U7.24
P0.14/A3: J20.6, U19.24
P0.14/A4: J29.6, U28.24
P0.14/A5: J38.6, U37.24
P0.14/A6: J47.6, U46.24
P0.14/A7: J56.6, U55.24
P0.14/A8: J65.6, U64.24
P0.15/A1: J11.7, U7.25
P0.15/A2: J3.7, U1.25
P0.15/A3: J20.7, U19.25
P0.15/A4: J29.7, U28.25
P0.15/A5: J38.7, U37.25
P0.15/A6: J47.7, U46.25
P0.15/A7: J56.7, U55.25
P0.15/A8: J65.7, U64.25
P0.16/A1: J11.8, U7.26
P0.16/A2: J20.8, U19.26
P0.16/A3: J3.8, U1.26
P0.16/A4: J29.8, U28.26
P0.16/A5: J38.8, U37.26
P0.16/A6: J47.8, U46.26
P0.16/A7: J56.8, U55.26
P0.16/A8: J65.8, U64.26
P0.17/A1: J11.9, U7.28
P0.17/A2: J20.9, U19.28
P0.17/A3: J29.9, U28.28
P0.17/A4: J3.9, U1.28
P0.17/A5: J38.9, U37.28
P0.17/A6: J47.9, U46.28
P0.17/A7: J56.9, U55.28
P0.17/A8: J65.9, U64.28
P0.18/A1: J11.10, U7.29
P0.18/A2: J20.10, U19.29
P0.18/A3: J29.10, U28.29
P0.18/A4: J38.10, U37.29
P0.18/A5: J3.10, U1.29
P0.18/A6: J47.10, U46.29
P0.18/A7: J56.10, U55.29
P0.18/A8: J65.10, U64.29
P0.19/SCK: J3.11, U1.30
P0.19/SCK1: J11.11, U7.30
P0.19/SCK2: J20.11, U19.30
P0.19/SCK3: J29.11, U28.30
P0.19/SCK4: J38.11, U37.30
P0.19/SCK5: J47.11, U46.30
P0.19/SCK6: J56.11, U55.30
P0.19/SCK7: J65.11, U64.30
P0.20/VBAT_MEAS: R3.1, R8.2, U1.35
P0.20/VBAT_MEAS1: R25.1, R26.2, U7.35
P0.20/VBAT_MEAS2: R47.1, R48.2, U19.35
P0.20/VBAT_MEAS3: R69.1, R70.2, U28.35
P0.20/VBAT_MEAS4: R91.1, R92.2, U37.35
P0.20/VBAT_MEAS5: R113.1, R114.2, U46.35
P0.20/VBAT_MEAS6: R135.1, R136.2, U55.35
P0.20/VBAT_MEAS7: R157.1, R158.2, U64.35
P0.21/COPI: J3.12, U1.37
P0.21/COPI1: J11.12, U7.37
P0.21/COPI2: J20.12, U19.37
P0.21/COPI3: J29.12, U28.37
P0.21/COPI4: J38.12, U37.37
P0.21/COPI5: J47.12, U46.37
P0.21/COPI6: J56.12, U55.37
P0.21/COPI7: J65.12, U64.37
P0.22/CIPO: J3.13, U1.38
P0.22/CIPO1: J11.13, U7.38
P0.22/CIPO2: J20.13, U19.38
P0.22/CIPO3: J29.13, U28.38
P0.22/CIPO4: J38.13, U37.38
P0.22/CIPO5: J47.13, U46.38
P0.22/CIPO6: J56.13, U55.38
P0.22/CIPO7: J65.13, U64.38
P0.23/RX: J3.14, U1.39
P0.23/RX1: J11.14, U7.39
P0.23/RX2: J20.14, U19.39
P0.23/RX3: J29.14, U28.39
P0.23/RX4: J38.14, U37.39
P0.23/RX5: J47.14, U46.39
P0.23/RX6: J56.14, U55.39
P0.23/RX7: J65.14, U64.39
P0.24/TX: J3.15, U1.40
P0.24/TX1: J11.15, U7.40
P0.24/TX2: J20.15, U19.40
P0.24/TX3: J29.15, U28.40
P0.24/TX4: J38.15, U37.40
P0.24/TX5: J47.15, U46.40
P0.24/TX6: J56.15, U55.40
P0.24/TX7: J65.15, U64.40
P0.25/VBAT_MEAS_EN: Q2.2, U1.42
P0.25/VBAT_MEAS_EN1: Q7.2, U7.42
P0.25/VBAT_MEAS_EN2: Q12.2, U19.42
P0.25/VBAT_MEAS_EN3: Q17.2, U28.42
P0.25/VBAT_MEAS_EN4: Q22.2, U37.42
P0.25/VBAT_MEAS_EN5: Q27.2, U46.42
P0.25/VBAT_MEAS_EN6: Q32.2, U55.42
P0.25/VBAT_MEAS_EN7: Q37.2, U64.42
P0.26/SDA: J2.12, J10.3, R17.1, U1.83, U8.6, U12.4
P0.26/SDA1: J9.12, J14.3, R38.1, U7.83, U13.6, U18.4
P0.26/SDA2: J19.12, J23.3, R60.1, U19.83, U22.6, U27.4
P0.26/SDA3: J28.12, J32.3, R82.1, U28.83, U31.6, U36.4
P0.26/SDA4: J37.12, J41.3, R104.1, U37.83, U40.6, U45.4
P0.26/SDA5: J46.12, J50.3, R126.1, U46.83, U49.6, U54.4
P0.26/SDA6: J55.12, J59.3, R148.1, U55.83, U58.6, U63.4
P0.26/SDA7: J64.12, J68.3, R170.1, U64.83, U67.6, U72.4
P0.27/SCL: J2.11, J10.4, R18.1, U1.84, U8.7, U12.1
P0.27/SCL1: J9.11, J14.4, R39.1, U7.84, U13.7, U18.1
P0.27/SCL2: J19.11, J23.4, R61.1, U19.84, U22.7, U27.1
P0.27/SCL3: J28.11, J32.4, R83.1, U28.84, U31.7, U36.1
P0.27/SCL4: J37.11, J41.4, R105.1, U37.84, U40.7, U45.1
P0.27/SCL5: J46.11, J50.4, R127.1, U46.84, U49.7, U54.1
P0.27/SCL6: J55.11, J59.4, R149.1, U55.84, U58.7, U63.1
P0.27/SCL7: J64.11, J68.4, R171.1, U64.84, U67.7, U72.1
P0.29/D1: J9.10, JMP3.P$2, U7.87
P0.29/D2: J2.10, JMP1.P$2, U1.87
P0.29/D3: J19.10, JMP5.P$2, U19.87
P0.29/D4: J28.10, JMP7.P$2, U28.87
P0.29/D5: J37.10, JMP9.P$2, U37.87
P0.29/D6: J46.10, JMP11.P$2, U46.87
P0.29/D7: J55.10, JMP13.P$2, U55.87
P0.29/D8: J64.10, JMP15.P$2, U64.87
P0.30/D1: J9.9, U7.88
P0.30/D2: J19.9, U19.88
P0.30/D3: J2.9, U1.88
P0.30/D4: J28.9, U28.88
P0.30/D5: J37.9, U37.88
P0.30/D6: J46.9, U46.88
P0.30/D7: J55.9, U55.88
P0.30/D8: J64.9, U64.88
P0.31/NRF_PS_EN: J3.16, JMP2.P$3, U1.89
P0.31/NRF_PS_EN1: J11.16, JMP4.P$3, U7.89
P0.31/NRF_PS_EN2: J20.16, JMP6.P$3, U19.89
P0.31/NRF_PS_EN3: J29.16, JMP8.P$3, U28.89
P0.31/NRF_PS_EN4: J38.16, JMP10.P$3, U37.89
P0.31/NRF_PS_EN5: J47.16, JMP12.P$3, U46.89
P0.31/NRF_PS_EN6: J56.16, JMP14.P$3, U55.89
P0.31/NRF_PS_EN7: J65.16, JMP16.P$3, U64.89
PROG: R12.2, U2.5
PROG1: R30.2, U16.5
PROG2: R52.2, U25.5
PROG3: R74.2, U34.5
PROG4: R96.2, U43.5
PROG5: R118.2, U52.5
PROG6: R140.2, U61.5
PROG7: R162.2, U70.5
PS_EN: Q5.3, R5.1, U3.6
PS_EN1: Q9.3, R34.1, U11.6
PS_EN2: Q14.3, R56.1, U21.6
PS_EN3: Q19.3, R78.1, U30.6
PS_EN4: Q24.3, R100.1, U39.6
PS_EN5: Q29.3, R122.1, U48.6
PS_EN6: Q34.3, R144.1, U57.6
PS_EN7: Q39.3, R166.1, U66.6
PS_EN_CC: R2.2, R5.2, U9.3, U9.6
PS_EN_CC1: R24.2, R34.2, U14.3, U14.6
PS_EN_CC2: R46.2, R56.2, U23.3, U23.6
PS_EN_CC3: R68.2, R78.2, U32.3, U32.6
PS_EN_CC4: R90.2, R100.2, U41.3, U41.6
PS_EN_CC5: R112.2, R122.2, U50.3, U50.6
PS_EN_CC6: R134.2, R144.2, U59.3, U59.6
PS_EN_CC7: R156.2, R166.2, U68.3, U68.6
RTC_INT: Q1.1, R6.1, U8.4
RTC_INT1: Q10.1, R37.1, U13.4
RTC_INT2: Q15.1, R59.1, U22.4
RTC_INT3: Q20.1, R81.1, U31.4
RTC_INT4: Q25.1, R103.1, U40.4
RTC_INT5: Q30.1, R125.1, U49.4
RTC_INT6: Q35.1, R147.1, U58.4
RTC_INT7: Q40.1, R169.1, U67.4
RTC_PS_EN: Q1.3, U9.5
RTC_PS_EN1: Q10.3, U14.5
RTC_PS_EN2: Q15.3, U23.5
RTC_PS_EN3: Q20.3, U32.5
RTC_PS_EN4: Q25.3, U41.5
RTC_PS_EN5: Q30.3, U50.5
RTC_PS_EN6: Q35.3, U59.5
RTC_PS_EN7: Q40.3, U68.5
SIM_CLK: J6.S3, TP3.TP, U1.46
SIM_CLK1: J18.S3, TP9.TP, U7.46
SIM_CLK2: J27.S3, TP15.TP, U19.46
SIM_CLK3: J36.S3, TP21.TP, U28.46
SIM_CLK4: J45.S3, TP27.TP, U37.46
SIM_CLK5: J54.S3, TP33.TP, U46.46
SIM_CLK6: J63.S3, TP39.TP, U55.46
SIM_CLK7: J72.S3, TP45.TP, U64.46
SIM_IO: J6.S6, TP6.TP, U1.48
SIM_IO1: J18.S6, TP12.TP, U7.48
SIM_IO2: J27.S6, TP18.TP, U19.48
SIM_IO3: J36.S6, TP24.TP, U28.48
SIM_IO4: J45.S6, TP30.TP, U37.48
SIM_IO5: J54.S6, TP36.TP, U46.48
SIM_IO6: J63.S6, TP42.TP, U55.48
SIM_IO7: J72.S6, TP48.TP, U64.48
SIM_RST: J6.S2, TP4.TP, U1.43
SIM_RST1: J18.S2, TP10.TP, U7.43
SIM_RST2: J27.S2, TP16.TP, U19.43
SIM_RST3: J36.S2, TP22.TP, U28.43
SIM_RST4: J45.S2, TP28.TP, U37.43
SIM_RST5: J54.S2, TP34.TP, U46.43
SIM_RST6: J63.S2, TP40.TP, U55.43
SIM_RST7: J72.S2, TP46.TP, U64.43
SIM_VCC: J6.S1, TP5.TP, U1.49
SIM_VCC1: J18.S1, TP11.TP, U7.49
SIM_VCC2: J27.S1, TP17.TP, U19.49
SIM_VCC3: J36.S1, TP23.TP, U28.49
SIM_VCC4: J45.S1, TP29.TP, U37.49
SIM_VCC5: J54.S1, TP35.TP, U46.49
SIM_VCC6: J63.S1, TP41.TP, U55.49
SIM_VCC7: J72.S1, TP47.TP, U64.49
SWCLK: J8.4, TP2.TP, U1.33
SWCLK1: J17.4, TP8.TP, U7.33
SWCLK2: J26.4, TP14.TP, U19.33
SWCLK3: J35.4, TP20.TP, U28.33
SWCLK4: J44.4, TP26.TP, U37.33
SWCLK5: J53.4, TP32.TP, U46.33
SWCLK6: J62.4, TP38.TP, U55.33
SWCLK7: J71.4, TP44.TP, U64.33
SWDIO: J8.2, TP1.TP, U1.34
SWDIO1: J17.2, TP7.TP, U7.34
SWDIO2: J26.2, TP13.TP, U19.34
SWDIO3: J35.2, TP19.TP, U28.34
SWDIO4: J44.2, TP25.TP, U37.34
SWDIO5: J53.2, TP31.TP, U46.34
SWDIO6: J62.2, TP37.TP, U55.34
SWDIO7: J71.2, TP43.TP, U64.34
VBAT: J2.1, J5.2, Q2.4, Q3.3, R10.2, U2.3
VBAT1: J9.1, J16.2, Q6.3, Q7.4, R27.2, U16.3
VBAT2: J19.1, J25.2, Q11.3, Q12.4, R49.2, U25.3
VBAT3: J28.1, J34.2, Q16.3, Q17.4, R71.2, U34.3
VBAT4: J37.1, J43.2, Q21.3, Q22.4, R93.2, U43.3
VBAT5: J46.1, J52.2, Q26.3, Q27.4, R115.2, U52.3
VBAT6: J55.1, J61.2, Q31.3, Q32.4, R137.2, U61.3
VBAT7: J64.1, J70.2, Q36.3, Q37.4, R159.2, U70.3
VBUS: C11.1, C13.1, C14.1, D5.A, D6.A, J1.VBUS1, J1.VBUS2, Q3.1, R7.2, R15.2, U2.4, U5.7, U9.2
VBUS1: C29.1, C30.1, C31.1, D7.A, D8.A, J15.VBUS1, J15.VBUS2, Q6.1, R22.2, R35.2, U14.2, U16.4, U17.7
VBUS2: C48.1, C49.1, C50.1, D11.A, D12.A, J24.VBUS1, J24.VBUS2, Q11.1, R45.2, R57.2, U23.2, U25.4, U26.7
VBUS3: C67.1, C68.1, C69.1, D15.A, D16.A, J33.VBUS1, J33.VBUS2, Q16.1, R67.2, R79.2, U32.2, U34.4, U35.7
VBUS4: C86.1, C87.1, C88.1, D19.A, D20.A, J42.VBUS1, J42.VBUS2, Q21.1, R89.2, R101.2, U41.2, U43.4, U44.7
VBUS5: C105.1, C106.1, C107.1, D23.A, D24.A, J51.VBUS1, J51.VBUS2, Q26.1, R111.2, R123.2, U50.2, U52.4, U53.7
VBUS6: C124.1, C125.1, C126.1, D27.A, D28.A, J60.VBUS1, J60.VBUS2, Q31.1, R133.2, R145.2, U59.2, U61.4, U62.7
VBUS7: C143.1, C144.1, C145.1, D31.A, D32.A, J69.VBUS1, J69.VBUS2, Q36.1, R155.2, R167.2, U68.2, U70.4, U71.7
VCC_5V0: D5.C, J2.3
VCC_5V1: D7.C, J9.3
VCC_5V2: D11.C, J19.3
VCC_5V3: D15.C, J28.3
VCC_5V4: D19.C, J37.3
VCC_5V5: D23.C, J46.3
VCC_5V6: D27.C, J55.3
VCC_5V7: D31.C, J64.3
VSYS: C6.1, C7.1, C17.1, D6.C, JMP2.P$1, Q1.2, Q3.2, R6.2, SW2.1, SW2.2, U3.5, U3.7, U3.8, U8.10
VSYS1: C22.1, C23.1, C35.1, D8.C, JMP4.P$1, Q6.2, Q10.2, R37.2, SW4.1, SW4.2, U11.5, U11.7, U11.8, U13.10
VSYS2: C41.1, C42.1, C54.1, D12.C, JMP6.P$1, Q11.2, Q15.2, R59.2, SW6.1, SW6.2, U21.5, U21.7, U21.8, U22.10
VSYS3: C60.1, C61.1, C73.1, D16.C, JMP8.P$1, Q16.2, Q20.2, R81.2, SW8.1, SW8.2, U30.5, U30.7, U30.8, U31.10
VSYS4: C79.1, C80.1, C92.1, D20.C, JMP10.P$1, Q21.2, Q25.2, R103.2, SW10.1, SW10.2, U39.5, U39.7, U39.8, U40.10
VSYS5: C98.1, C99.1, C111.1, D24.C, JMP12.P$1, Q26.2, Q30.2, R125.2, SW12.1, SW12.2, U48.5, U48.7, U48.8, U49.10
VSYS6: C117.1, C118.1, C130.1, D28.C, JMP14.P$1, Q31.2, Q35.2, R147.2, SW14.1, SW14.2, U57.5, U57.7, U57.8, U58.10
VSYS7: C136.1, C137.1, C149.1, D32.C, JMP16.P$1, Q36.2, Q40.2, R169.2, SW16.1, SW16.2, U66.5, U66.7, U66.8, U67.10

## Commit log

2020-09-18 First commit of nRF9160 Thing Plus
2020-10-07 Changed C9 to match other 4.7u caps. Update D5/D6 to BAT60A Updated J5 to match Sparkfun's JST connector
2020-10-19 Modifying mode pin to be connected directly to the MD button. (useful for external wakeup)
2020-10-30 Adding LIS2DH12TR and supporting components. Adding jumpers for D2 (Accel int) and also PS_EN
2020-10-30 Adding XYZ label
2020-10-30 Thing Plus label
2020-10-30 Updated name label and eSIM cream
2020-11-10 Moved components to local libraries
    Parts not in SFE Eagle libraries were moved to local temporary libraries with the SFE SKUs added for the BOM
2020-12-01 Updating SDA/SCL labels
2020-12-02 Adding Cortex-m header. Removing tag connect. Removing external SIM bits. Changing SIM holder to cheaper variant.
2020-12-02 Moving programming header up to get away from board edge.
2021-01-07 Changing flash to W25Q32JVZPIQ. Changing D5/6 to BAT20J.
2021-01-07 Ignoring autosaves.
2021-01-07 Adding test points for SIM
2021-01-12 SF Update
    - Added PROD_ID info to new parts in temp libraries
    - Moved new parts to temp libraries
    - Added second fiducial to the top side of the board
    - Rotated buzzard labels for GPIO 0/SDA and 1/SCL to match the other labels
    - Shifted U9, R2, R7 to prevent overlap with reset label
    - Removed date text on layer 22 (bPlace) and replaced with version text on bottom copper layer
2021-01-12 Cleaned up silkscreen labels around U9, R2, R7 Fixed some of the text related to fab export drawings.
2021-01-13 Added Production Panel
    -Added production panel
    -Moved brd,sch, and library files to Hardware folder
2021-01-13 Panel Fix
    Issues spotted:
    - USB-C connector was a two layer part instead of four. This caused an issue where the inner 3.3V copper layer was shorting to the ground layers on other layers through the USB support tabs.
    - Running the panelizer tool cause Eagle to crash.
    Changes Made:
    - Replaced USB-C connector with 4-layer footprint varient
    - Not sure what was causing Eagle to crash, but rotating the board 90 degrees fixed it
2021-01-13 Moved Panel Files
    Moved panel files out of hardware folder
2021-01-14 Updated nRF9160 paste footprint
    reduced the paste aperatures on some ground pads to minimize solder shorts
2021-03-31 Updated BOM
    replaced SW1 and SW2 to new taller momentary switch
2021-06-15 Making adjustments to power supply
    Changed:
    * Pin 7 of U3 grounded.
